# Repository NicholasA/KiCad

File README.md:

# KiCad
General KiCad Project Files

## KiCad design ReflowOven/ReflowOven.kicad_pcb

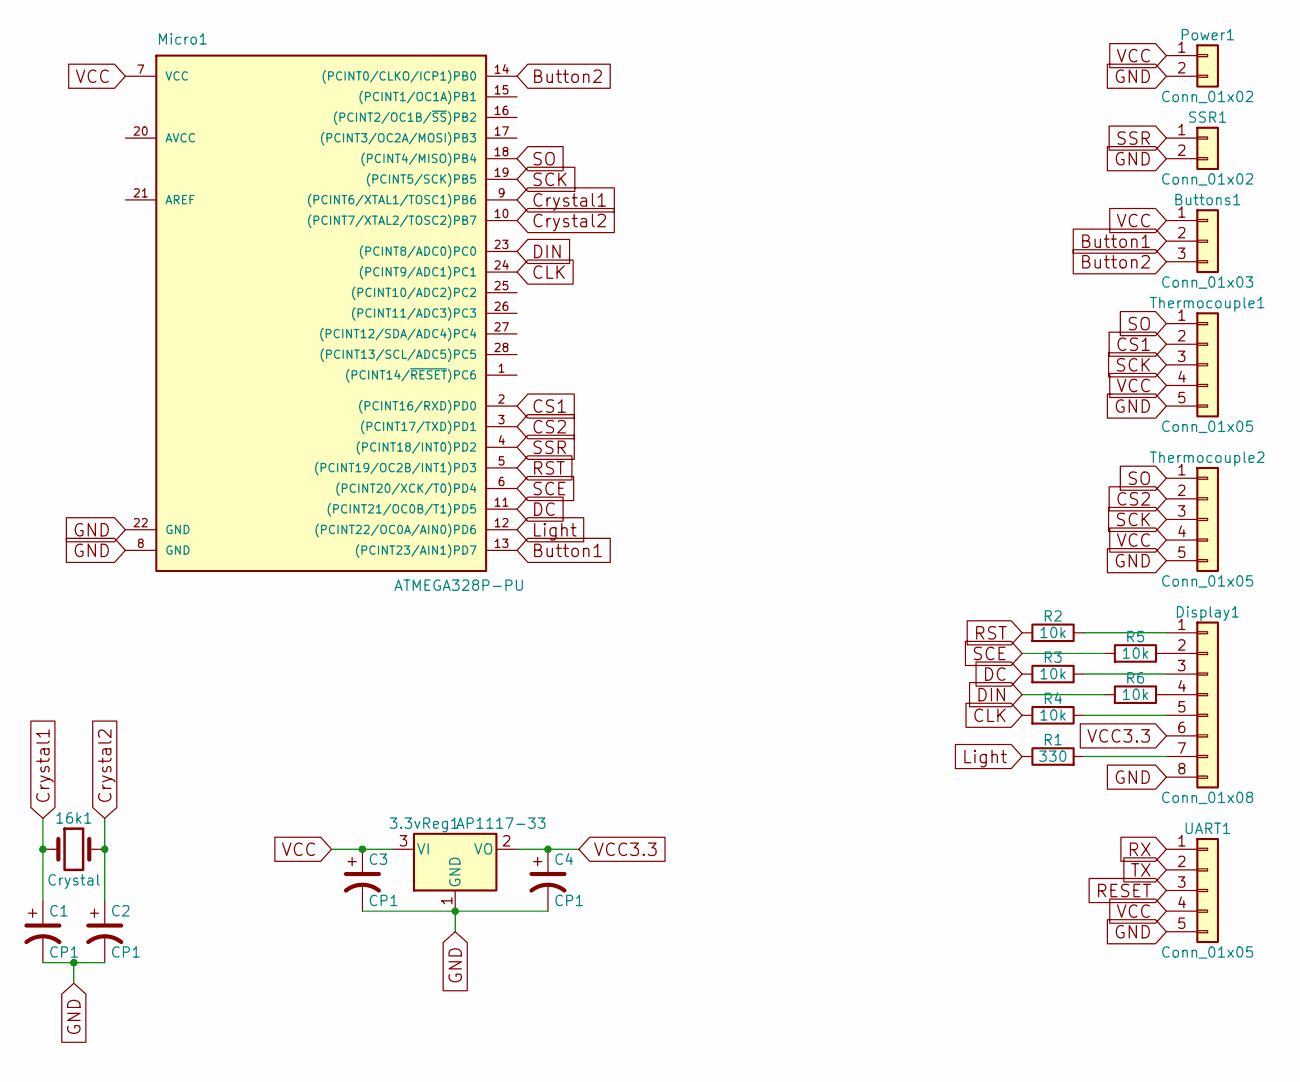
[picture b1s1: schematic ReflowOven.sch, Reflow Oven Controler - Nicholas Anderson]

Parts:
3.3vReg1: AP1117-33; SOT-223
16k1: Crystal; Crystal_HC49-4H_Vertical
Buttons1: Conn_01x03; Pin_Header_Straight_1x03_Pitch2.54mm
C1, C2, C3, C4: CP1; C_0805_HandSoldering
Display1: Conn_01x08; Pin_Header_Straight_1x08_Pitch2.54mm
Micro1: ATMEGA328P-PU; DIP-28_W7.62mm_Socket
Power1: Conn_01x02; Pin_Header_Straight_1x02_Pitch2.54mm
R1: 330; R_0805_HandSoldering
R2, R3, R4, R5, R6: 10k; R_0805_HandSoldering
SSR1: Conn_01x02; Pin_Header_Straight_1x02_Pitch2.54mm
Thermocouple1, Thermocouple2: Conn_01x05; Pin_Header_Straight_1x05_Pitch2.54mm
UART1: Conn_01x05; Pin_Header_Straight_1x05_Pitch2.54mm

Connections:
Button1: Buttons1.2, Micro1.13 ((PCINT23/AIN1)PD7)
Button2: Buttons1.3, Micro1.14 ((PCINT0/CLKO/ICP1)PB0)
CLK: Micro1.24 ((PCINT9/ADC1)PC1), R4.2
CS1: Micro1.2 ((PCINT16/RXD)PD0), Thermocouple1.2
CS2: Micro1.3 ((PCINT17/TXD)PD1), Thermocouple2.2
Crystal1: 16k1.1, C1.1, Micro1.9 ((PCINT6/XTAL1/TOSC1)PB6)
Crystal2: 16k1.2, C2.1, Micro1.10 ((PCINT7/XTAL2/TOSC2)PB7)
DC: Micro1.11 ((PCINT21/OC0B/T1)PD5), R3.2
DIN: Micro1.23 ((PCINT8/ADC0)PC0), R6.2
GND: 3.3vReg1.1 (GND), C1.2, C2.2, C3.2, C4.2, Display1.8, Micro1.8 (GND), Micro1.22 (GND), Power1.2, SSR1.2, Thermocouple1.5, Thermocouple2.5, UART1.5
Light: Micro1.12 ((PCINT22/OC0A/AIN0)PD6), R1.1
unnamed: Display1.1, R2.1
unnamed: Display1.2, R5.1
unnamed: Display1.3, R3.1
unnamed: Display1.4, R6.1
unnamed: Display1.5, R4.1
unnamed: Display1.7, R1.2
RESET: UART1.3
RST: Micro1.5 ((PCINT19/OC2B/INT1)PD3), R2.2
RX: UART1.1
SCE: Micro1.6 ((PCINT20/XCK/T0)PD4), R5.2
SCK: Micro1.19 ((PCINT5/SCK)PB5), Thermocouple1.3, Thermocouple2.3
SO: Micro1.18 ((PCINT4/MISO)PB4), Thermocouple1.1, Thermocouple2.1
SSR: Micro1.4 ((PCINT18/INT0)PD2), SSR1.1
TX: UART1.2
VCC: 3.3vReg1.3 (VI), Buttons1.1, C3.1, Micro1.7 (VCC), Power1.1, Thermocouple1.4, Thermocouple2.4, UART1.4
VCC3.3: 3.3vReg1.2 (VO), C4.1, Display1.6

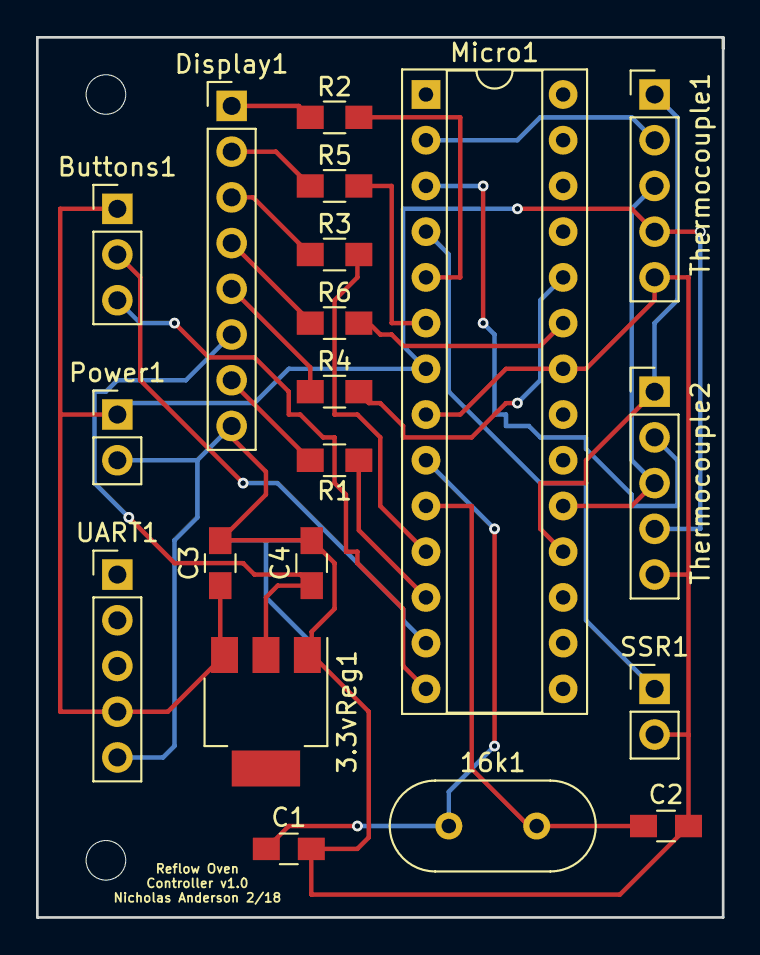
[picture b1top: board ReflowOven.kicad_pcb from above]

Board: 2 copper layers, 38.1 x 48.9 mm, 20 parts (0 on the bottom side), 24 nets.

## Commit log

2018-02-22 ReflowOven Project added
